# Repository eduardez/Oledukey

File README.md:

# Oledukey
Aun en fase de diseño, pero pinta flama.

# Renders

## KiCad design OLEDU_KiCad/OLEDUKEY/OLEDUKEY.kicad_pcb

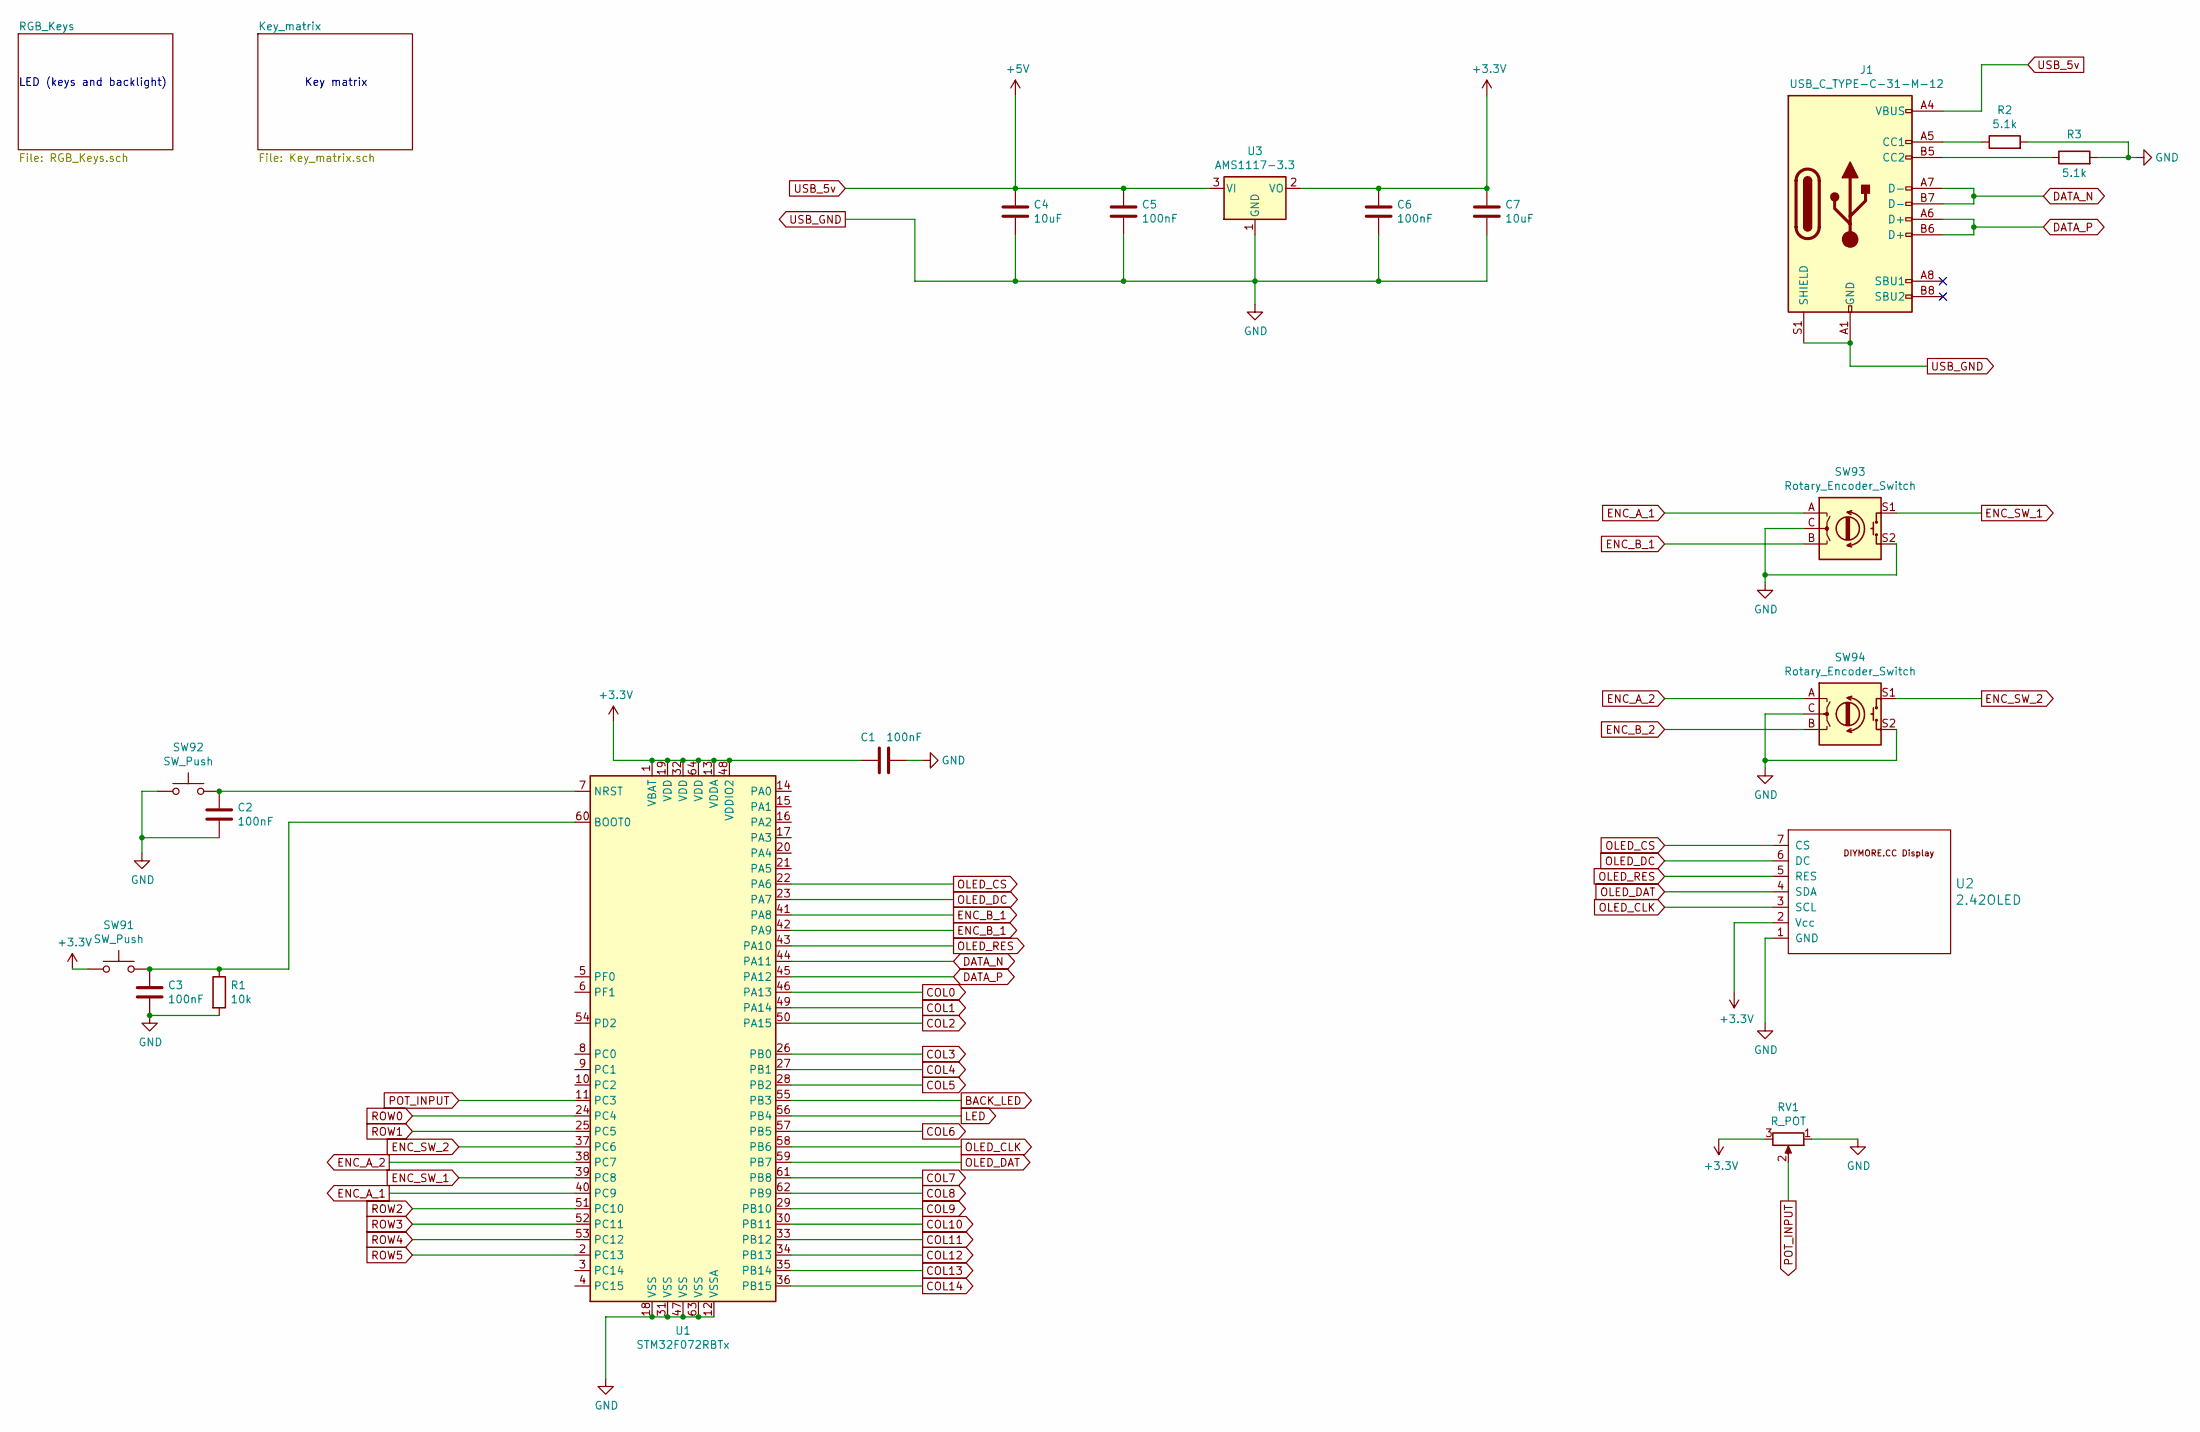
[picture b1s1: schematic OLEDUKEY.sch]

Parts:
C1, C2, C3, C5, C6: 100nF; C_0603_1608Metric_Pad1.08x0.95mm_HandSolder
C4, C7: 10uF; C_0603_1608Metric_Pad1.08x0.95mm_HandSolder
J1: USB_C_TYPE-C-31-M-12; USB_C_Receptacle_HRO_TYPE-C-31-M-12
R1: 10k; R_Axial_DIN0204_L3.6mm_D1.6mm_P7.62mm_Horizontal; Part URL Home
R2, R3: 5.1k; R_Axial_DIN0204_L3.6mm_D1.6mm_P7.62mm_Horizontal; Part URL Home
RV1: R_POT; Potentiometer_Bourns_PTA6043_Single_Slide
SW91, SW92: SW_Push; SW_SPST_TL3342
SW93, SW94: Rotary_Encoder_Switch; RotaryEncoder_Alps_EC11E-Switch_Vertical_H20mm
U1: STM32F072RBTx; LQFP-64_10x10mm_P0.5mm
U2: 2.42OLED; DIYMORE.CC
U3: AMS1117-3.3; SOT-223-3_TabPin2

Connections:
+3V3: C1.1, C6.1, C7.1, RV1.3, SW91.1, U1.1 (VBAT), U1.13 (VDDA), U1.19 (VDD), U1.32 (VDD), U1.48 (VDDIO2), U1.64 (VDD), U2.2 (Vcc), U3.2 (VO)
BACK_LED: U1.55 (PB3); also elsewhere on the board
COL0: U1.46 (PA13); also elsewhere on the board
COL1: U1.49 (PA14); also elsewhere on the board
COL2: U1.50 (PA15); also elsewhere on the board
COL3: U1.26 (PB0); also elsewhere on the board
COL4: U1.27 (PB1); also elsewhere on the board
COL5: U1.28 (PB2); also elsewhere on the board
COL6: U1.57 (PB5); also elsewhere on the board
COL7: U1.61 (PB8); also elsewhere on the board
COL8: U1.62 (PB9); also elsewhere on the board
COL9: U1.29 (PB10); also elsewhere on the board
COL10: U1.30 (PB11); also elsewhere on the board
COL11: U1.33 (PB12); also elsewhere on the board
COL12: U1.34 (PB13); also elsewhere on the board
COL13: U1.35 (PB14); also elsewhere on the board
COL14: U1.36 (PB15); also elsewhere on the board
DATA_N: J1.A7 (D-), J1.B7 (D-), U1.44 (PA11)
DATA_P: J1.A6 (D+), J1.B6 (D+), U1.45 (PA12)
ENC_A_1: SW93.A, U1.40 (PC9)
ENC_A_2: SW94.A, U1.38 (PC7)
ENC_SW_1: SW93.S1, U1.39 (PC8)
ENC_SW_2: SW94.S1, U1.37 (PC6)
LED: U1.56 (PB4); also elsewhere on the board
unnamed: C2.1, SW92.2, U1.7 (NRST)
unnamed: C3.1, R1.1, SW91.2, U1.60 (BOOT0)
unnamed: J1.A5 (CC1), R2.1
unnamed: J1.B5 (CC2), R3.1
OLED_CLK: U1.58 (PB6), U2.3 (SCL)
OLED_CS: U1.22 (PA6), U2.7 (CS)
OLED_DAT: U1.59 (PB7), U2.4 (SDA)
OLED_DC: U1.23 (PA7), U2.6 (DC)
OLED_RES: U1.43 (PA10), U2.5 (RES)
POT_INPUT: RV1.2, U1.11 (PC3)
ROW0: U1.24 (PC4); also elsewhere on the board
ROW1: U1.25 (PC5); also elsewhere on the board
ROW2: U1.51 (PC10); also elsewhere on the board
ROW3: U1.52 (PC11); also elsewhere on the board
ROW4: U1.53 (PC12); also elsewhere on the board
ROW5: U1.2 (PC13); also elsewhere on the board
USB_GND: C1.2, C2.2, C3.2, C4.2, C5.2, C6.2, C7.2, J1.A1 (GND), J1.A12 (GND), J1.B1 (GND), J1.B12 (GND), J1.S1 (SHIELD), R1.2, R2.2, R3.2, RV1.1, SW92.1, SW93.C, SW93.S2, SW94.C, SW94.S2, U1.12 (VSSA), U1.18 (VSS), U1.31 (VSS), U1.47 (VSS), U1.63 (VSS), U2.1 (GND), U3.1 (GND); also elsewhere on the board

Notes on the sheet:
LED (keys and backlight)
Key matrix

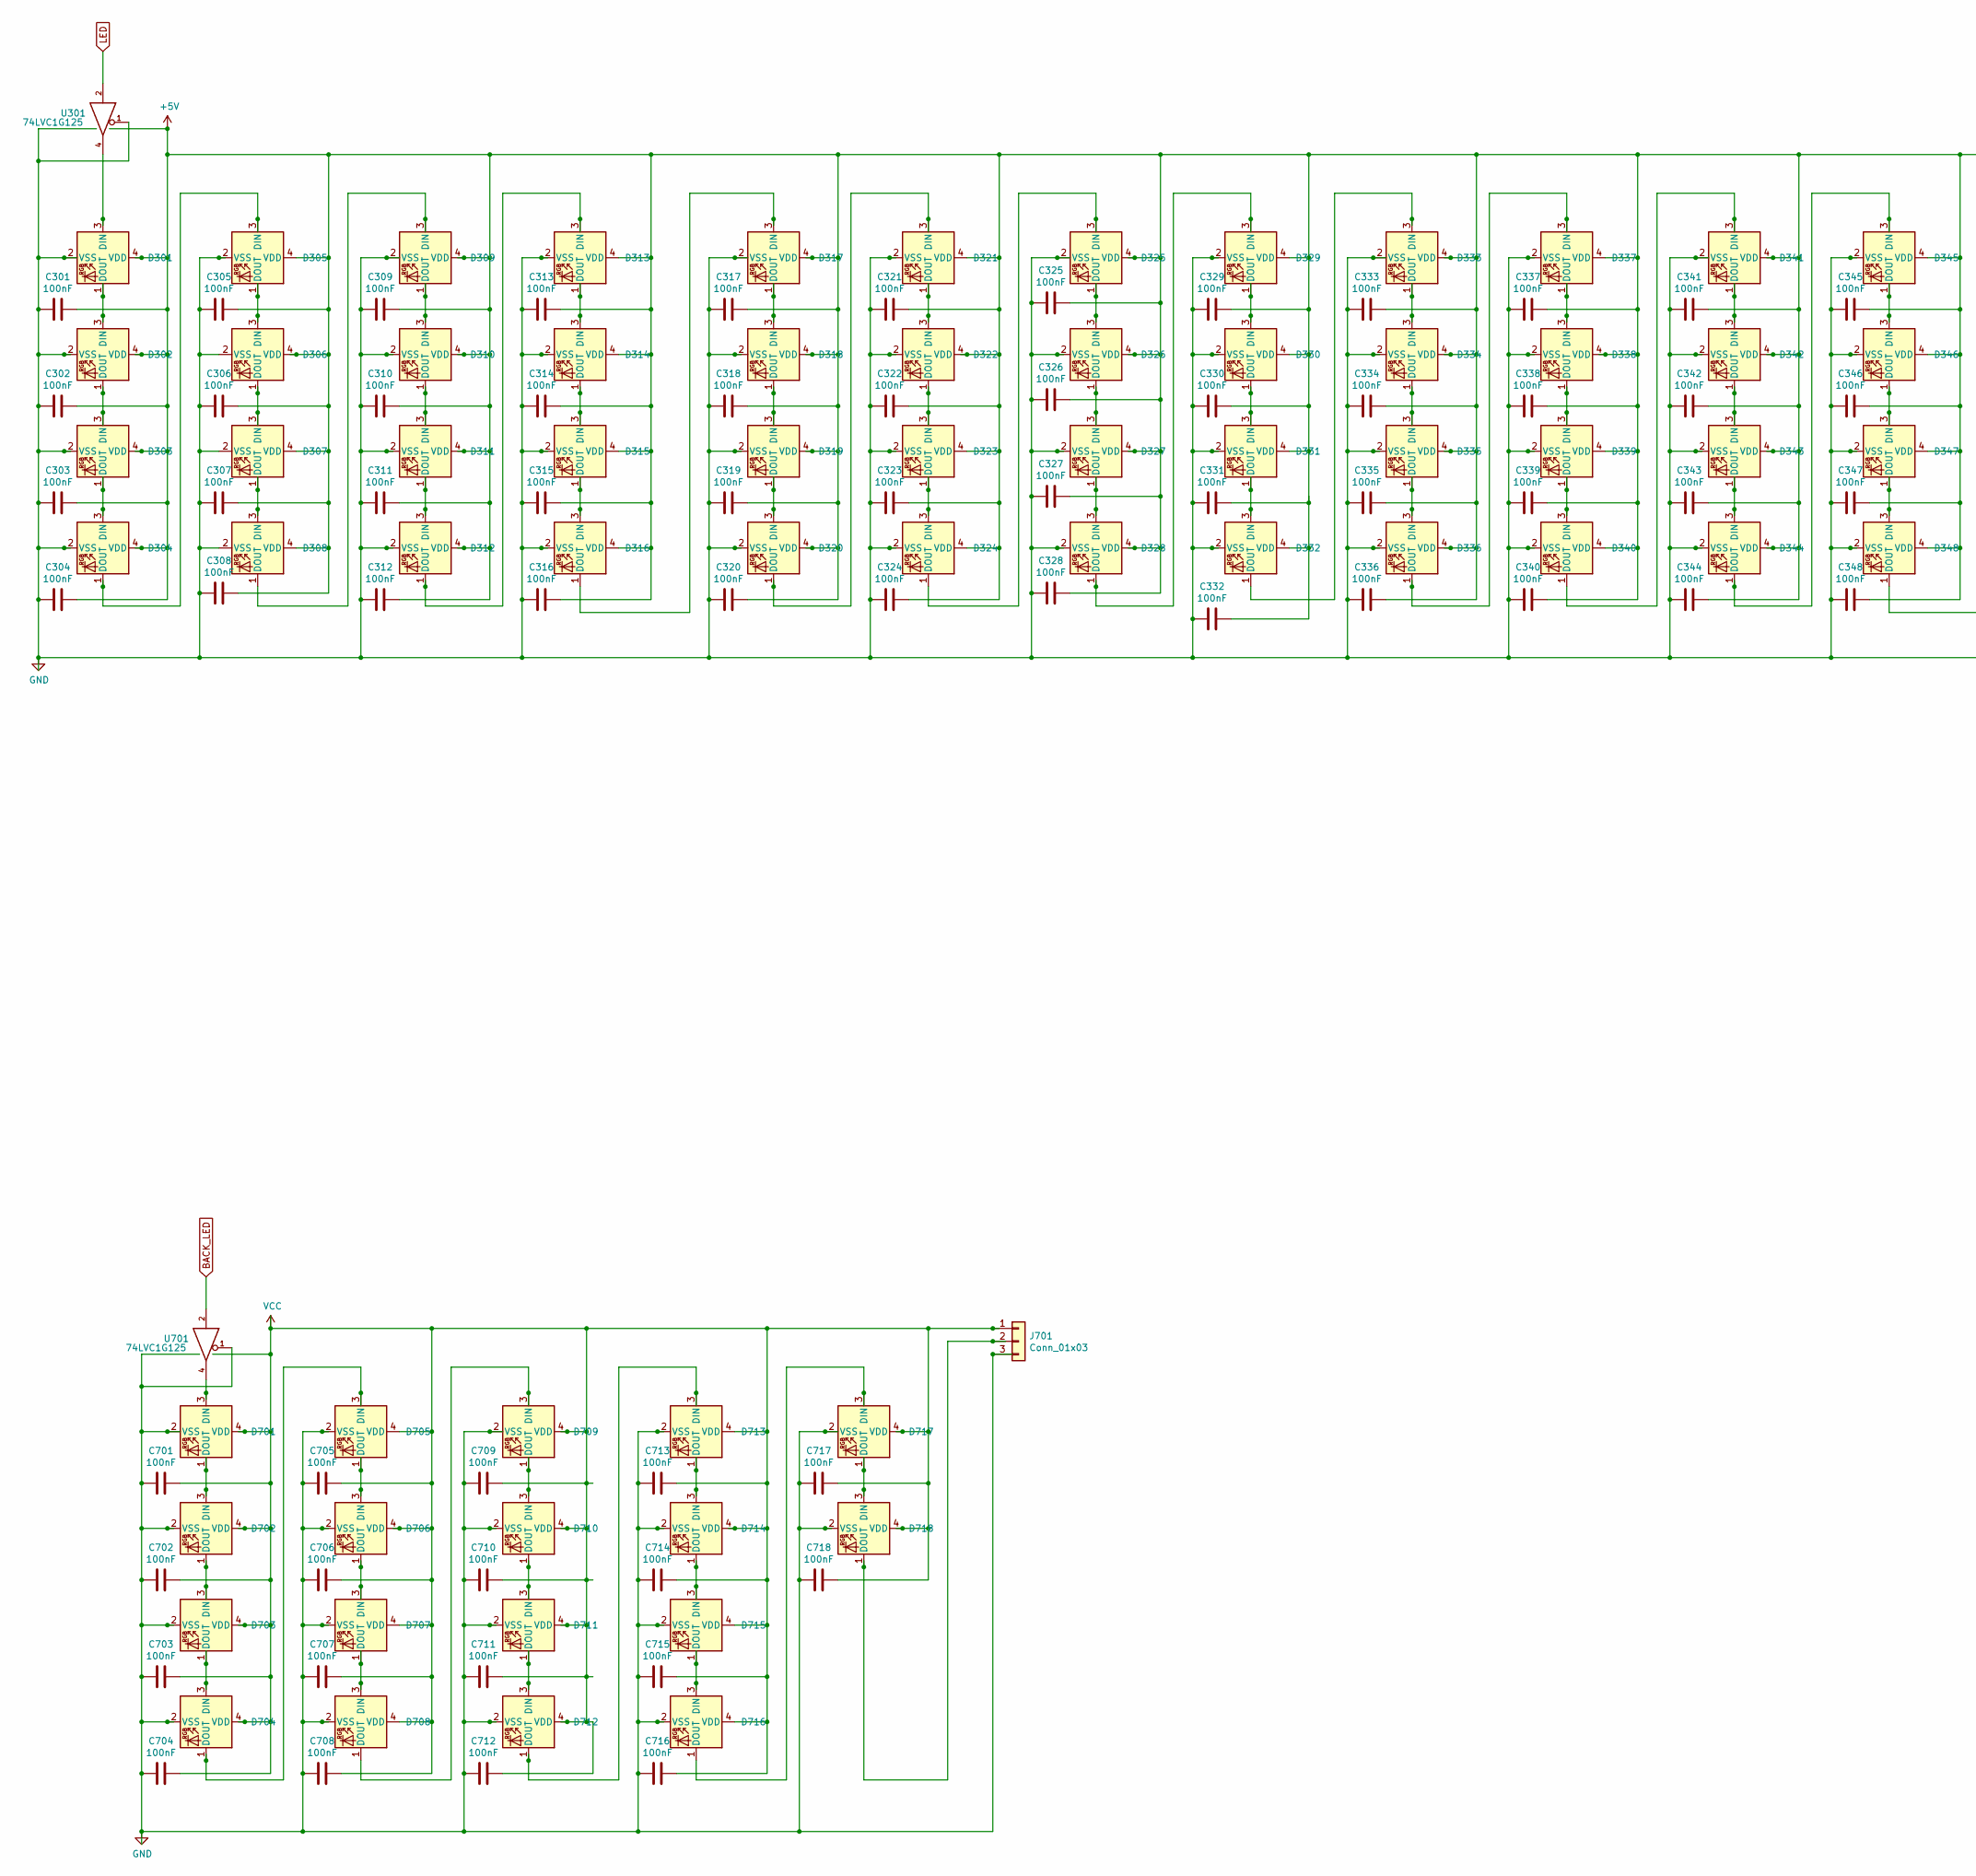
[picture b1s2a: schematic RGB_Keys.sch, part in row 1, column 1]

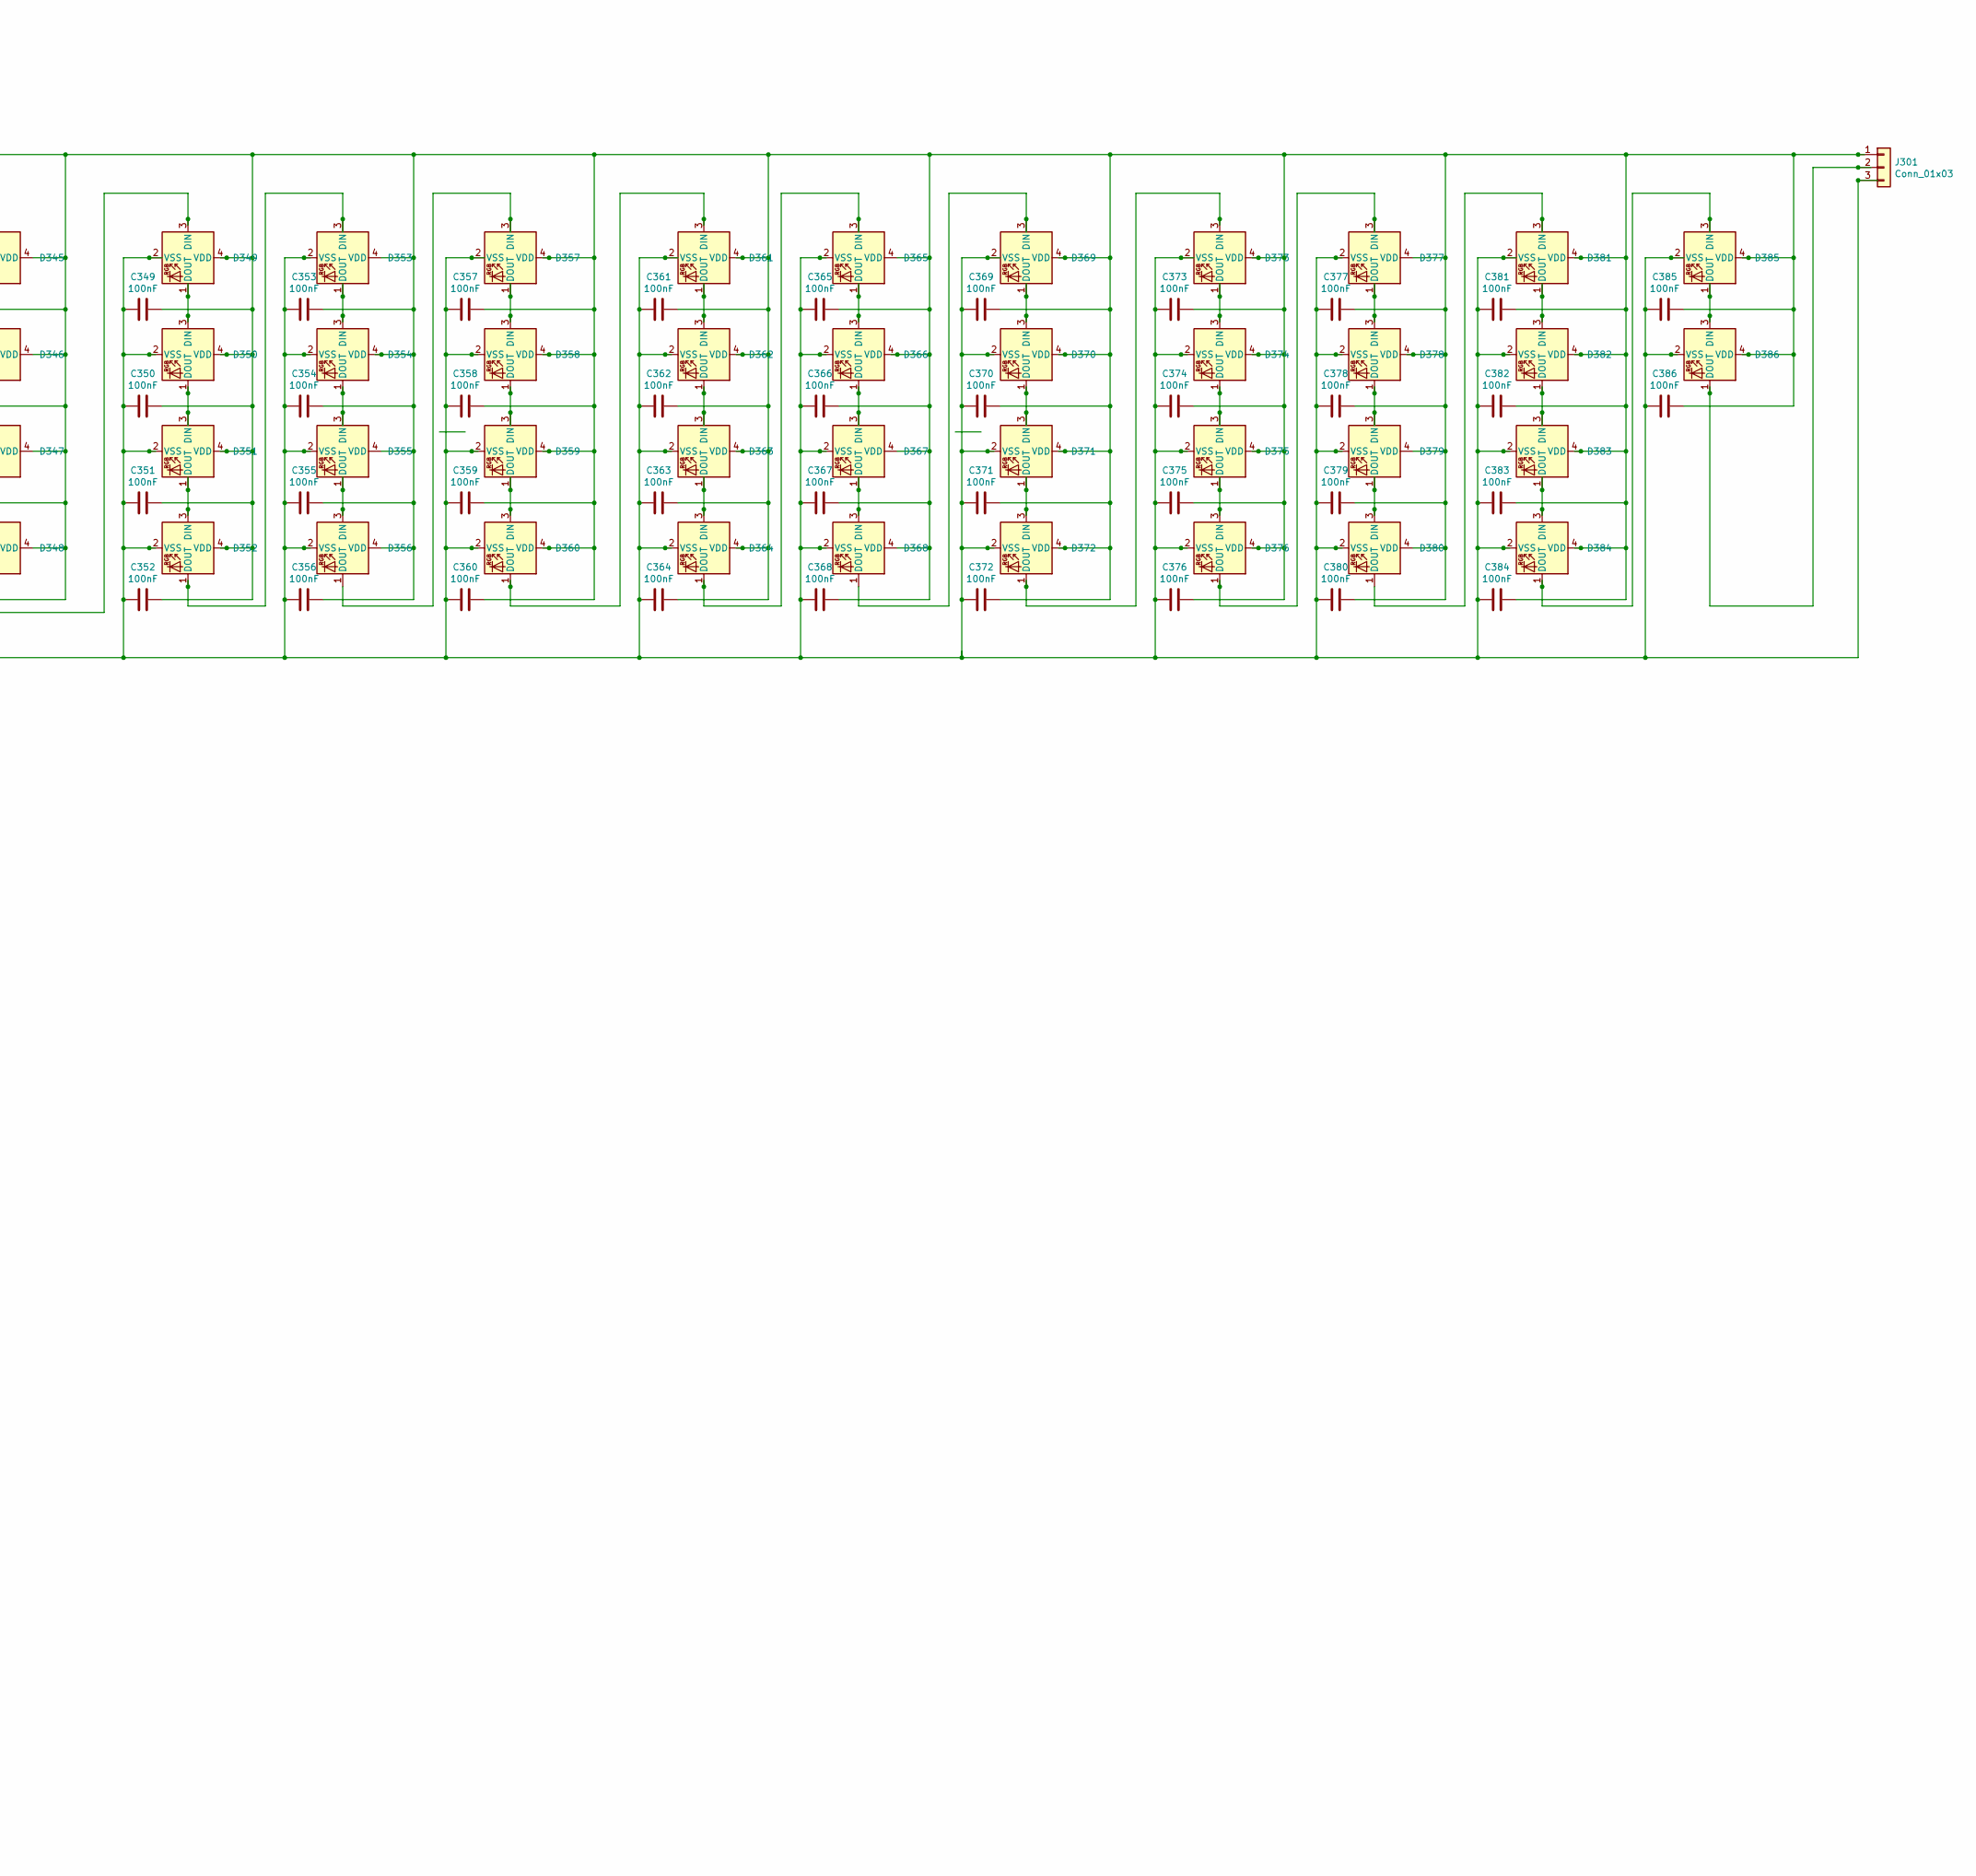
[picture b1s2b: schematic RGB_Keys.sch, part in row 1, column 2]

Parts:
C301, C302, C303, C304, C305, C306, C307, C308, C309, C310, C311, C312, C313, C314, C315, C316, C317, C318, C319, C320, C321, C322, C323, C324, C325, C326, C327, C328, C329, C330, C331, C332, C333, C334, C335, C336, C337, C338, C339, C340, C341, C342, C343, C344, C345, C346, C347, C348, C349, C350, C351, C352, C353, C354, C355, C356, C357, C358, C359, C360, C361, C362, C363, C364, C365, C366, C367, C368, C369, C370, C371, C372, C373, C374, C375, C376, C377, C378, C379, C380, C381, C382, C383, C384, C385, C386, C701, C702, C703, C704, C705, C706, C707, C708, C709, C710, C711, C712, C713, C714, C715, C716, C717, C718: 100nF; C_0603_1608Metric_Pad1.08x0.95mm_HandSolder
D301, D302, D303, D304, D305, D306, D307, D308, D309, D310, D311, D312, D313, D314, D315, D316, D317, D318, D319, D320, D321, D322, D323, D324, D325, D326, D327, D328, D329, D330, D331, D332, D333, D334, D335, D336, D337, D338, D339, D340, D341, D342, D343, D344, D345, D346, D347, D348, D349, D350, D351, D352, D353, D354, D355, D356, D357, D358, D359, D360, D361, D362, D363, D364, D365, D366, D367, D368, D369, D370, D371, D372, D373, D374, D375, D376, D377, D378, D379, D380, D381, D382, D383, D384, D385, D386: SK6812MINI; SK6812-MINI-E
D701, D702, D703, D704, D705, D706, D707, D708, D709, D710, D711, D712, D713, D714, D715, D716, D717, D718: SK6812MINI; LED_SK6812MINI_PLCC4_3.5x3.5mm_P1.75mm
J301, J701: Conn_01x03; PinHeader_1x03_P2.54mm_Vertical; Part URL Home
U301, U701: 74LVC1G125; SOT-23-5

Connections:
BACK_LED: U701.2; also elsewhere on the board
LED: U301.2; also elsewhere on the board
unnamed: D301.1 (DOUT), D302.3 (DIN)
unnamed: D301.3 (DIN), U301.4
unnamed: D302.1 (DOUT), D303.3 (DIN)
unnamed: D303.1 (DOUT), D304.3 (DIN)
unnamed: D304.1 (DOUT), D305.3 (DIN)
unnamed: D305.1 (DOUT), D306.3 (DIN)
unnamed: D306.1 (DOUT), D307.3 (DIN)
unnamed: D307.1 (DOUT), D308.3 (DIN)
unnamed: D308.1 (DOUT), D309.3 (DIN)
unnamed: D309.1 (DOUT), D310.3 (DIN)
unnamed: D310.1 (DOUT), D311.3 (DIN)
unnamed: D311.1 (DOUT), D312.3 (DIN)
unnamed: D312.1 (DOUT), D313.3 (DIN)
unnamed: D313.1 (DOUT), D314.3 (DIN)
unnamed: D314.1 (DOUT), D315.3 (DIN)
unnamed: D315.1 (DOUT), D316.3 (DIN)
unnamed: D316.1 (DOUT), D317.3 (DIN)
unnamed: D317.1 (DOUT), D318.3 (DIN)
unnamed: D318.1 (DOUT), D319.3 (DIN)
unnamed: D319.1 (DOUT), D320.3 (DIN)
unnamed: D320.1 (DOUT), D321.3 (DIN)
unnamed: D321.1 (DOUT), D322.3 (DIN)
unnamed: D322.1 (DOUT), D323.3 (DIN)
unnamed: D323.1 (DOUT), D324.3 (DIN)
unnamed: D324.1 (DOUT), D325.3 (DIN)
unnamed: D325.1 (DOUT), D326.3 (DIN)
unnamed: D326.1 (DOUT), D327.3 (DIN)
unnamed: D327.1 (DOUT), D328.3 (DIN)
unnamed: D328.1 (DOUT), D329.3 (DIN)
unnamed: D329.1 (DOUT), D330.3 (DIN)
unnamed: D330.1 (DOUT), D331.3 (DIN)
unnamed: D331.1 (DOUT), D332.3 (DIN)
unnamed: D332.1 (DOUT), D333.3 (DIN)
unnamed: D333.1 (DOUT), D334.3 (DIN)
unnamed: D334.1 (DOUT), D335.3 (DIN)
unnamed: D335.1 (DOUT), D336.3 (DIN)
unnamed: D336.1 (DOUT), D337.3 (DIN)
unnamed: D337.1 (DOUT), D338.3 (DIN)
unnamed: D338.1 (DOUT), D339.3 (DIN)
unnamed: D339.1 (DOUT), D340.3 (DIN)
unnamed: D340.1 (DOUT), D341.3 (DIN)
unnamed: D341.1 (DOUT), D342.3 (DIN)
unnamed: D342.1 (DOUT), D343.3 (DIN)
unnamed: D343.1 (DOUT), D344.3 (DIN)
unnamed: D344.1 (DOUT), D345.3 (DIN)
unnamed: D345.1 (DOUT), D346.3 (DIN)
unnamed: D346.1 (DOUT), D347.3 (DIN)
unnamed: D347.1 (DOUT), D348.3 (DIN)
unnamed: D348.1 (DOUT), D349.3 (DIN)
unnamed: D349.1 (DOUT), D350.3 (DIN)
unnamed: D350.1 (DOUT), D351.3 (DIN)
unnamed: D351.1 (DOUT), D352.3 (DIN)
unnamed: D352.1 (DOUT), D353.3 (DIN)
unnamed: D353.1 (DOUT), D354.3 (DIN)
unnamed: D354.1 (DOUT), D355.3 (DIN)
unnamed: D355.1 (DOUT), D356.3 (DIN)
unnamed: D356.1 (DOUT), D357.3 (DIN)
unnamed: D357.1 (DOUT), D358.3 (DIN)
unnamed: D358.1 (DOUT), D359.3 (DIN)
unnamed: D359.1 (DOUT), D360.3 (DIN)
unnamed: D360.1 (DOUT), D361.3 (DIN)
unnamed: D361.1 (DOUT), D362.3 (DIN)
unnamed: D362.1 (DOUT), D363.3 (DIN)
unnamed: D363.1 (DOUT), D364.3 (DIN)
unnamed: D364.1 (DOUT), D365.3 (DIN)
unnamed: D365.1 (DOUT), D366.3 (DIN)
unnamed: D366.1 (DOUT), D367.3 (DIN)
unnamed: D367.1 (DOUT), D368.3 (DIN)
unnamed: D368.1 (DOUT), D369.3 (DIN)
unnamed: D369.1 (DOUT), D370.3 (DIN)
unnamed: D370.1 (DOUT), D371.3 (DIN)
unnamed: D371.1 (DOUT), D372.3 (DIN)
unnamed: D372.1 (DOUT), D373.3 (DIN)
unnamed: D373.1 (DOUT), D374.3 (DIN)
unnamed: D374.1 (DOUT), D375.3 (DIN)
unnamed: D375.1 (DOUT), D376.3 (DIN)
unnamed: D376.1 (DOUT), D377.3 (DIN)
unnamed: D377.1 (DOUT), D378.3 (DIN)
unnamed: D378.1 (DOUT), D379.3 (DIN)
unnamed: D379.1 (DOUT), D380.3 (DIN)
unnamed: D380.1 (DOUT), D381.3 (DIN)
unnamed: D381.1 (DOUT), D382.3 (DIN)
unnamed: D382.1 (DOUT), D383.3 (DIN)
unnamed: D383.1 (DOUT), D384.3 (DIN)
unnamed: D384.1 (DOUT), D385.3 (DIN)
unnamed: D385.1 (DOUT), D386.3 (DIN)
unnamed: D386.1 (DOUT), J301.2
unnamed: D701.1 (DOUT), D702.3 (DIN)
unnamed: D701.3 (DIN), U701.4
unnamed: D702.1 (DOUT), D703.3 (DIN)
unnamed: D703.1 (DOUT), D704.3 (DIN)
unnamed: D704.1 (DOUT), D705.3 (DIN)
unnamed: D705.1 (DOUT), D706.3 (DIN)
unnamed: D706.1 (DOUT), D707.3 (DIN)
unnamed: D707.1 (DOUT), D708.3 (DIN)
unnamed: D708.1 (DOUT), D709.3 (DIN)
unnamed: D709.1 (DOUT), D710.3 (DIN)
unnamed: D710.1 (DOUT), D711.3 (DIN)
unnamed: D711.1 (DOUT), D712.3 (DIN)
unnamed: D712.1 (DOUT), D713.3 (DIN)
unnamed: D713.1 (DOUT), D714.3 (DIN)
unnamed: D714.1 (DOUT), D715.3 (DIN)
unnamed: D715.1 (DOUT), D716.3 (DIN)
unnamed: D716.1 (DOUT), D717.3 (DIN)
unnamed: D717.1 (DOUT), D718.3 (DIN)
unnamed: D718.1 (DOUT), J701.2
USB_GND: C301.2, C302.2, C303.2, C304.2, C305.2, C306.2, C307.2, C308.2, C309.2, C310.2, C311.2, C312.2, C313.2, C314.2, C315.2, C316.2, C317.2, C318.2, C319.2, C320.2, C321.2, C322.2, C323.2, C324.2, C325.2, C326.2, C327.2, C328.2, C329.2, C330.2, C331.2, C332.2, C333.2, C334.2, C335.2, C336.2, C337.2, C338.2, C339.2, C340.2, C341.2, C342.2, C343.2, C344.2, C345.2, C346.2, C347.2, C348.2, C349.2, C350.2, C351.2, C352.2, C353.2, C354.2, C355.2, C356.2, C357.2, C358.2, C359.2, C360.2, C361.2, C362.2, C363.2, C364.2, C365.2, C366.2, C367.2, C368.2, C369.2, C370.2, C371.2, C372.2, C373.2, C374.2, C375.2, C376.2, C377.2, C378.2, C379.2, C380.2, C381.2, C382.2, C383.2, C384.2, C385.2, C386.2, C701.2, C702.2, C703.2, C704.2, C705.2, C706.2, C707.2, C708.2, C709.2, C710.2, C711.2, C712.2, C713.2, C714.2, C715.2, C716.2, C717.2, C718.2, D301.2 (VSS), D302.2 (VSS), D303.2 (VSS), D304.2 (VSS), D305.2 (VSS), D306.2 (VSS), D307.2 (VSS), D308.2 (VSS), D309.2 (VSS), D310.2 (VSS), D311.2 (VSS), D312.2 (VSS), D313.2 (VSS), D314.2 (VSS), D315.2 (VSS), D316.2 (VSS), D317.2 (VSS), D318.2 (VSS), D319.2 (VSS), D320.2 (VSS), D321.2 (VSS), D322.2 (VSS), D323.2 (VSS), D324.2 (VSS), D325.2 (VSS), D326.2 (VSS), D327.2 (VSS), D328.2 (VSS), D329.2 (VSS), D330.2 (VSS), D331.2 (VSS), D332.2 (VSS), D333.2 (VSS), D334.2 (VSS), D335.2 (VSS), D336.2 (VSS), D337.2 (VSS), D338.2 (VSS), D339.2 (VSS), D340.2 (VSS), D341.2 (VSS), D342.2 (VSS), D343.2 (VSS), D344.2 (VSS), D345.2 (VSS), D346.2 (VSS), D347.2 (VSS), D348.2 (VSS), D349.2 (VSS), D350.2 (VSS), D351.2 (VSS), D352.2 (VSS), D353.2 (VSS), D354.2 (VSS), D355.2 (VSS), D356.2 (VSS), D357.2 (VSS), D358.2 (VSS), D359.2 (VSS), D360.2 (VSS), D361.2 (VSS), D362.2 (VSS), D363.2 (VSS), D364.2 (VSS), D365.2 (VSS), D366.2 (VSS), D367.2 (VSS), D368.2 (VSS), D369.2 (VSS), D370.2 (VSS), D371.2 (VSS), D372.2 (VSS), D373.2 (VSS), D374.2 (VSS), D375.2 (VSS), D376.2 (VSS), D377.2 (VSS), D378.2 (VSS), D379.2 (VSS), D380.2 (VSS), D381.2 (VSS), D382.2 (VSS), D383.2 (VSS), D384.2 (VSS), D385.2 (VSS), D386.2 (VSS), D701.2 (VSS), D702.2 (VSS), D703.2 (VSS), D704.2 (VSS), D705.2 (VSS), D706.2 (VSS), D707.2 (VSS), D708.2 (VSS), D709.2 (VSS), D710.2 (VSS), D711.2 (VSS), D712.2 (VSS), D713.2 (VSS), D714.2 (VSS), D715.2 (VSS), D716.2 (VSS), D717.2 (VSS), D718.2 (VSS), J301.3, J701.3, U301.1, U301.3 (GND), U701.1, U701.3 (GND); also elsewhere on the board

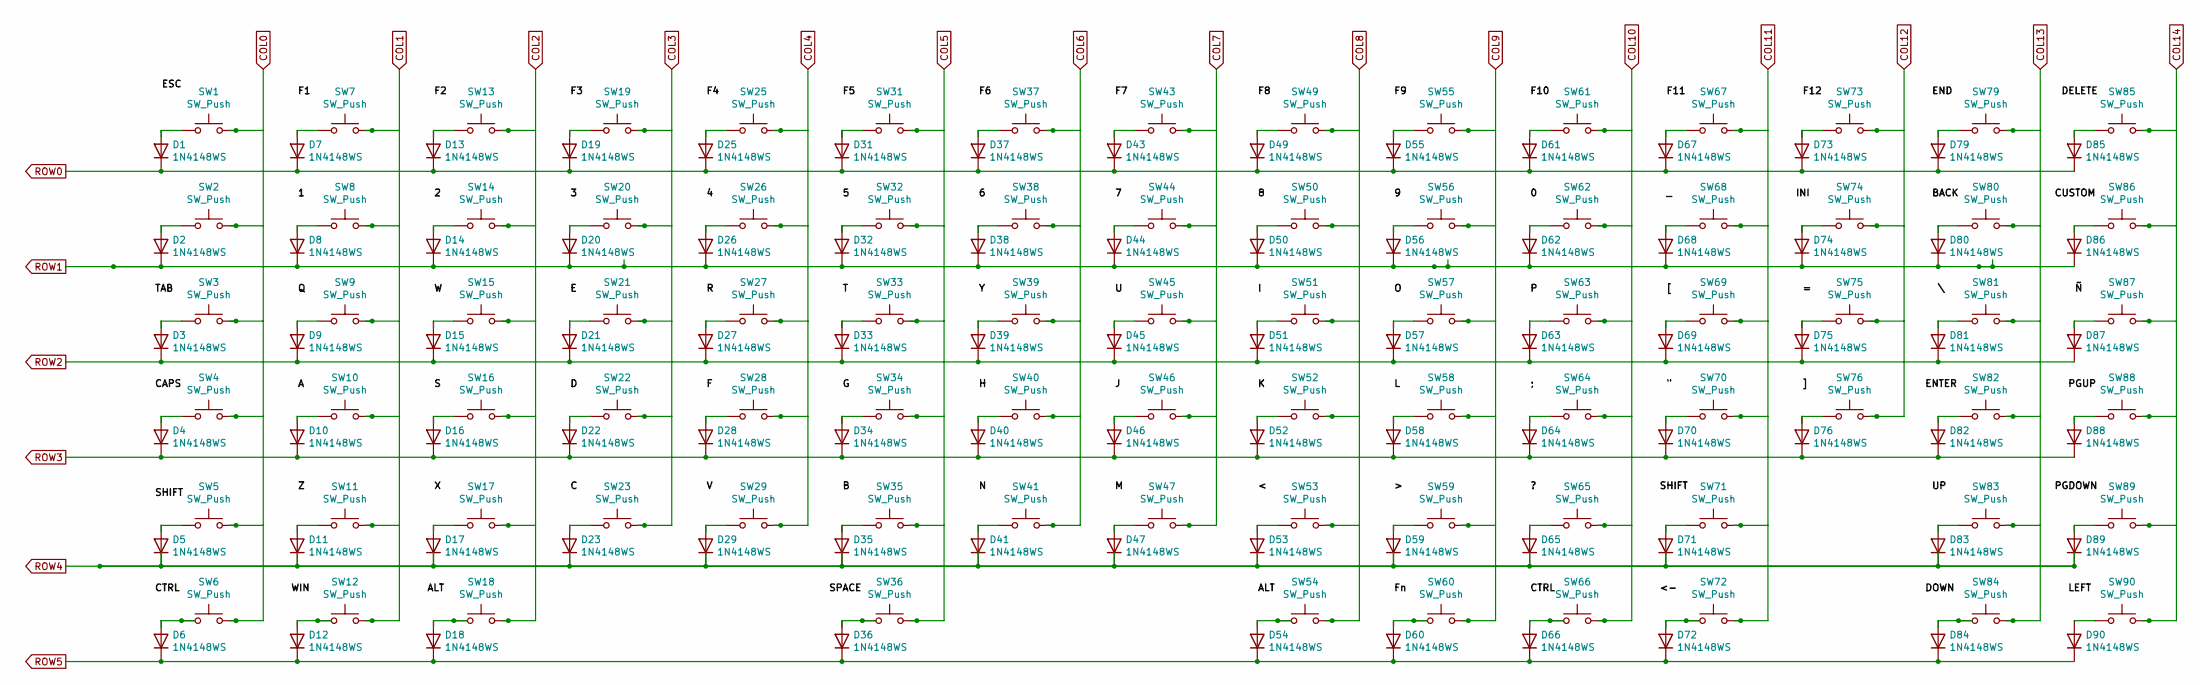
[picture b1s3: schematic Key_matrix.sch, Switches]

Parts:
D1, D2, D3, D4, D5, D6, D7, D8, D9, D10, D11, D12, D13, D14, D15, D16, D17, D18, D19, D20, D21, D22, D23, D25, D26, D27, D28, D29, D31, D32, D33, D34, D35, D36, D37, D38, D39, D40, D41, D43, D44, D45, D46, D47, D49, D50, D51, D52, D53, D54, D55, D56, D57, D58, D59, D60, D61, D62, D63, D64, D65, D66, D67, D68, D69, D70, D71, D72, D73, D74, D75, D76, D79, D80, D81, D82, D83, D84, D85, D86, D87, D88, D89, D90: 1N4148WS; D_0603_1608Metric
SW1, SW2, SW7, SW8, SW9, SW10, SW11, SW13, SW14, SW15, SW16, SW17, SW19, SW20, SW21, SW22, SW23, SW25, SW26, SW27, SW28, SW29, SW31, SW32, SW33, SW34, SW35, SW37, SW38, SW39, SW40, SW41, SW43, SW44, SW45, SW46, SW47, SW49, SW50, SW51, SW52, SW53, SW54, SW55, SW56, SW57, SW58, SW59, SW60, SW61, SW62, SW63, SW64, SW65, SW66, SW67, SW68, SW69, SW70, SW72, SW73, SW74, SW75, SW76, SW79, SW83, SW84, SW85, SW86, SW87, SW88, SW89, SW90: SW_Push; SW_Cherry_MX_1.00u_PCB
SW3, SW81: SW_Push; SW_Cherry_MX_1.50u_PCB
SW4, SW71: SW_Push; SW_Cherry_MX_1.75u_PCB
SW5, SW82: SW_Push; SW_Cherry_MX_2.25u_PCB
SW6, SW12, SW18: SW_Push; SW_Cherry_MX_1.25u_PCB
SW36: SW_Push; SW_Cherry_MX_6.25u_PCB
SW80: SW_Push; SW_Cherry_MX_2.00u_PCB

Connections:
COL0: SW1.2, SW2.2, SW3.2, SW4.2, SW5.2, SW6.2; also elsewhere on the board
COL1: SW7.2, SW8.2, SW9.2, SW10.2, SW11.2, SW12.2; also elsewhere on the board
COL2: SW13.2, SW14.2, SW15.2, SW16.2, SW17.2, SW18.2; also elsewhere on the board
COL3: SW19.2, SW20.2, SW21.2, SW22.2, SW23.2; also elsewhere on the board
COL4: SW25.2, SW26.2, SW27.2, SW28.2, SW29.2; also elsewhere on the board
COL5: SW31.2, SW32.2, SW33.2, SW34.2, SW35.2, SW36.2; also elsewhere on the board
COL6: SW37.2, SW38.2, SW39.2, SW40.2, SW41.2; also elsewhere on the board
COL7: SW43.2, SW44.2, SW45.2, SW46.2, SW47.2; also elsewhere on the board
COL8: SW49.2, SW50.2, SW51.2, SW52.2, SW53.2, SW54.2; also elsewhere on the board
COL9: SW55.2, SW56.2, SW57.2, SW58.2, SW59.2, SW60.2; also elsewhere on the board
COL10: SW61.2, SW62.2, SW63.2, SW64.2, SW65.2, SW66.2; also elsewhere on the board
COL11: SW67.2, SW68.2, SW69.2, SW70.2, SW71.2, SW72.2; also elsewhere on the board
COL12: SW73.2, SW74.2, SW75.2, SW76.2; also elsewhere on the board
COL13: SW79.2, SW80.2, SW81.2, SW82.2, SW83.2, SW84.2; also elsewhere on the board
COL14: SW85.2, SW86.2, SW87.2, SW88.2, SW89.2, SW90.2; also elsewhere on the board
unnamed: D1.2 (A), SW1.1
unnamed: D2.2 (A), SW2.1
unnamed: D3.2 (A), SW3.1
unnamed: D4.2 (A), SW4.1
unnamed: D5.2 (A), SW5.1
unnamed: D6.2 (A), SW6.1
unnamed: D7.2 (A), SW7.1
unnamed: D8.2 (A), SW8.1
unnamed: D9.2 (A), SW9.1
unnamed: D10.2 (A), SW10.1
unnamed: D11.2 (A), SW11.1
unnamed: D12.2 (A), SW12.1
unnamed: D13.2 (A), SW13.1
unnamed: D14.2 (A), SW14.1
unnamed: D15.2 (A), SW15.1
unnamed: D16.2 (A), SW16.1
unnamed: D17.2 (A), SW17.1
unnamed: D18.2 (A), SW18.1
unnamed: D19.2 (A), SW19.1
unnamed: D20.2 (A), SW20.1
unnamed: D21.2 (A), SW21.1
unnamed: D22.2 (A), SW22.1
unnamed: D23.2 (A), SW23.1
unnamed: D25.2 (A), SW25.1
unnamed: D26.2 (A), SW26.1
unnamed: D27.2 (A), SW27.1
unnamed: D28.2 (A), SW28.1
unnamed: D29.2 (A), SW29.1
unnamed: D31.2 (A), SW31.1
unnamed: D32.2 (A), SW32.1
unnamed: D33.2 (A), SW33.1
unnamed: D34.2 (A), SW34.1
unnamed: D35.2 (A), SW35.1
unnamed: D36.2 (A), SW36.1
unnamed: D37.2 (A), SW37.1
unnamed: D38.2 (A), SW38.1
unnamed: D39.2 (A), SW39.1
unnamed: D40.2 (A), SW40.1
unnamed: D41.2 (A), SW41.1
unnamed: D43.2 (A), SW43.1
unnamed: D44.2 (A), SW44.1
unnamed: D45.2 (A), SW45.1
unnamed: D46.2 (A), SW46.1
unnamed: D47.2 (A), SW47.1
unnamed: D49.2 (A), SW49.1
unnamed: D50.2 (A), SW50.1
unnamed: D51.2 (A), SW51.1
unnamed: D52.2 (A), SW52.1
unnamed: D53.2 (A), SW53.1
unnamed: D54.2 (A), SW54.1
unnamed: D55.2 (A), SW55.1
unnamed: D56.2 (A), SW56.1
unnamed: D57.2 (A), SW57.1
unnamed: D58.2 (A), SW58.1
unnamed: D59.2 (A), SW59.1
unnamed: D60.2 (A), SW60.1
unnamed: D61.2 (A), SW61.1
unnamed: D62.2 (A), SW62.1
unnamed: D63.2 (A), SW63.1
unnamed: D64.2 (A), SW64.1
unnamed: D65.2 (A), SW65.1
unnamed: D66.2 (A), SW66.1
unnamed: D67.2 (A), SW67.1
unnamed: D68.2 (A), SW68.1
unnamed: D69.2 (A), SW69.1
unnamed: D70.2 (A), SW70.1
unnamed: D71.2 (A), SW71.1
unnamed: D72.2 (A), SW72.1
unnamed: D73.2 (A), SW73.1
unnamed: D74.2 (A), SW74.1
unnamed: D75.2 (A), SW75.1
unnamed: D76.2 (A), SW76.1
unnamed: D79.2 (A), SW79.1
unnamed: D80.2 (A), SW80.1
unnamed: D81.2 (A), SW81.1
unnamed: D82.2 (A), SW82.1
unnamed: D83.2 (A), SW83.1
unnamed: D84.2 (A), SW84.1
unnamed: D85.2 (A), SW85.1
unnamed: D86.2 (A), SW86.1
unnamed: D87.2 (A), SW87.1
unnamed: D88.2 (A), SW88.1
unnamed: D89.2 (A), SW89.1
unnamed: D90.2 (A), SW90.1
ROW0: D1.1 (K), D7.1 (K), D13.1 (K), D19.1 (K), D25.1 (K), D31.1 (K), D37.1 (K), D43.1 (K), D49.1 (K), D55.1 (K), D61.1 (K), D67.1 (K), D73.1 (K), D79.1 (K), D85.1 (K); also elsewhere on the board
ROW1: D2.1 (K), D8.1 (K), D14.1 (K), D20.1 (K), D26.1 (K), D32.1 (K), D38.1 (K), D44.1 (K), D50.1 (K), D56.1 (K), D62.1 (K), D68.1 (K), D74.1 (K), D80.1 (K), D86.1 (K); also elsewhere on the board
ROW2: D3.1 (K), D9.1 (K), D15.1 (K), D21.1 (K), D27.1 (K), D33.1 (K), D39.1 (K), D45.1 (K), D51.1 (K), D57.1 (K), D63.1 (K), D69.1 (K), D75.1 (K), D81.1 (K), D87.1 (K); also elsewhere on the board
ROW3: D4.1 (K), D10.1 (K), D16.1 (K), D22.1 (K), D28.1 (K), D34.1 (K), D40.1 (K), D46.1 (K), D52.1 (K), D58.1 (K), D64.1 (K), D70.1 (K), D76.1 (K), D82.1 (K), D88.1 (K); also elsewhere on the board
ROW4: D5.1 (K), D11.1 (K), D17.1 (K), D23.1 (K), D29.1 (K), D35.1 (K), D41.1 (K), D47.1 (K), D53.1 (K), D59.1 (K), D65.1 (K), D71.1 (K), D83.1 (K), D89.1 (K); also elsewhere on the board
ROW5: D6.1 (K), D12.1 (K), D18.1 (K), D36.1 (K), D54.1 (K), D60.1 (K), D66.1 (K), D72.1 (K), D84.1 (K), D90.1 (K); also elsewhere on the board

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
